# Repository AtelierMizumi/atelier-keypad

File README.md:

# Atelier6K

A 6-key mechanical keypad with 3 extra buttons, designed for osu! and usable as
a small macropad. ATmega32U4, USB-C, hot-swap sockets, per-key and underglow
RGB, QMK firmware with VIA.

**[Live demo](https://blog.minhthuan.dev/atelier-keypad/)**: switch between
rev 0, rev 1 and the planned rev 2, rotate each board in 3D, pull the case
apart, and try rapid trigger in the browser.

| Revision | State | Read |
|---|---|---|
| Rev 0 (2022, ATmega32U4) | Original files, unchanged | [Looking back at rev 0](docs/rev0-review.md), [defect review](docs/design-review.md) |
| Rev 1 (2026, RP2040) | Order files ready (ERC 0, DRC 0); not built | [How it is made](docs/rev1-board.md), [honest grade](docs/rev1-assessment.md) |
| Rev 2.0 (Hall effect, 8 kHz) | Order files, firmware and CI ready (ERC 0, DRC 0); not built; branch `plan/hall-effect` | [How to order](https://github.com/AtelierMizumi/atelier-keypad/blob/plan/hall-effect/docs/build/ordering.md), [the board](https://github.com/AtelierMizumi/atelier-keypad/blob/plan/hall-effect/docs/rev2-board.md), [bring-up](https://github.com/AtelierMizumi/atelier-keypad/blob/plan/hall-effect/docs/rev2-bringup.md) |

> [!WARNING]
> **Rev 0 is an unverified prototype.** It was designed in 2022 as a first PCB
> and has no recorded bring-up. A [design review](docs/design-review.md) found
> issues that should be fixed before anyone orders it, including a missing
> fuse and an LED chain the firmware cannot drive. Treat the files as a
> reference, not as a board ready to manufacture.

## Features

- 6 Cherry MX switches on Kailh hot-swap sockets, plus 3 tactile buttons, in a
  3 × 3 diode matrix
- Per-key reverse-mount RGB (6 LEDs) and underglow (4 LEDs)
- ATmega32U4 with a 16 MHz crystal, USB-C with ESD protection
- QMK firmware with VIA, 1000 Hz polling and runtime-adjustable debounce (rev 1 firmware)
- Stacked laser-cut acrylic case, 14 mm tall, generated from the PCB file
- 2-layer PCB, about 81 × 74 mm, hand-solderable parts (0805, SOD-123, TQFP-44)

## Renders

| Top | Bottom |
|-----|--------|
|  |  |

Schematic: [SVG](docs/images/schematic.svg)

### Case

Four laser-cut acrylic layers that follow the PCB outline and clamp the board
between them with four M3 screws. The cut files are generated from the KiCad
board, so cut-outs and screw holes always match the PCB.

| Layer | Acrylic | Job |
|-------|---------|-----|
| Switch plate | 3 mm clear | Locates the switches; top face 5.0 mm above the PCB |
| Top frame | 2 mm clear | Spacer that sets the switch height |
| Bottom frame | 5 mm frosted | Clears the sockets and spreads the underglow |
| Base | 3 mm clear | Captive M3 nuts, reset hole |

DXF files are in [`case/dxf/`](case/dxf). Materials, cutting notes and
assembly steps are in the [case design notes](docs/case.md). The case has not
been cut or test-fitted yet.

## Rev 1 (designed, not built)

`hardware/rev1/` holds the next revision: an RP2040-Zero module, 9 direct
pins, one chain of 10 SK6812MINI-E LEDs, a polyfuse and a level shifter, on
the same outline and screw holes. The schematic, board and routing are
generated from `hardware/rev1/circuit.py` by `scripts/rev1.sh` and pass
KiCad's ERC and DRC. It has not been fabricated; see
[docs/rev1-board.md](docs/rev1-board.md) for the open points before ordering.

## Repository layout

| Path | Contents |
|------|----------|
| `hardware/atelier6k/` | Rev 0 KiCad 6 project (schematic and PCB), unchanged since 2022 |
| `hardware/libs/` | Footprint and symbol libraries (git submodules) and local footprints |
| `hardware/gerbers/rev0/` | Gerbers and drill files exported in 2022 |
| `hardware/bom.csv` | Bill of materials generated from the schematic |
| `firmware/atelier6k/` | Rev 1 QMK keyboard (RP2040), runtime debounce and its tests |
| `firmware/via/` | VIA v3 definition with the debounce menu |
| `firmware/build/` | Built firmware (`atelier6k_default.uf2`) |
| `firmware/legacy-2022/` | Rev 0 firmware and its 2022 build |
| `case/` | Case generator (`generate.py`), its tests, DXF cut files; 2022 drawings in `legacy/` |
| `docs/` | Design review, case notes, ERC/DRC reports, schematic, images |
| `site/` | The demo page published to GitHub Pages |
| `scripts/` | `export.sh` regenerates all derived files; `check-assets.sh` checks image links |

Clone with submodules:

```sh
git clone --recurse-submodules https://github.com/AtelierMizumi/atelier-keypad.git
```

The original KiCad 6 files are kept under the tag `rev0-kicad6`.

## Regenerating renders and reports

`scripts/export.sh` runs `kicad-cli` (KiCad 10 or newer) from your system, or
from the official KiCad Docker image when KiCad is not installed:

```sh
./scripts/export.sh          # renders, GLB, schematic SVG, BOM, ERC/DRC, case DXF
./scripts/check-assets.sh    # fails if any image reference leaves the repo
```

## Firmware

`firmware/atelier6k/` is the rev 1 firmware for current QMK (0.34.8): RP2040,
nine direct-pin keys, one chain of ten RGB LEDs, VIA.

- **1000 Hz** USB polling.
- **Debounce adjustable at runtime**, 0–25 ms, from a slider in VIA. A press
  is reported on the scan that first sees it; the debounce time only delays
  the release. The setting is stored on the keypad.
- **Three mode layers**, osu! standard, taiko and mania, switched with a side
  button and shown by the underglow colour. Every key is remappable in VIA.
- Brightness capped at 120 of 255 to stay inside the USB current budget.

It has been compiled and its debounce logic is unit-tested, but it has **not
run on hardware**: rev 1 of the board does not exist yet. The pin assignment
in `keyboard.json` matches the routed rev 1 PCB, and a test in
`hardware/rev1/tests/` fails if the two ever disagree.

```sh
./scripts/firmware.sh        # unit tests, lint, build firmware/build/atelier6k_default.uf2
```

The script needs Docker and a QMK checkout; see the comment at its top.
To use the VIA menu, load `firmware/via/atelier6k.json` in VIA's Design tab.

The 2022 firmware for the rev 0 ATmega32U4 board is kept in
`firmware/legacy-2022/`; it does not build on current QMK.

## License

- Hardware (`hardware/`, `case/`): [CERN-OHL-P v2](LICENSES/CERN-OHL-P-2.0.txt)
- Firmware (`firmware/`): [GPL-2.0-or-later](LICENSES/GPL-2.0-or-later.txt), as required by QMK
- Third-party libraries under `hardware/libs/` keep their own licenses

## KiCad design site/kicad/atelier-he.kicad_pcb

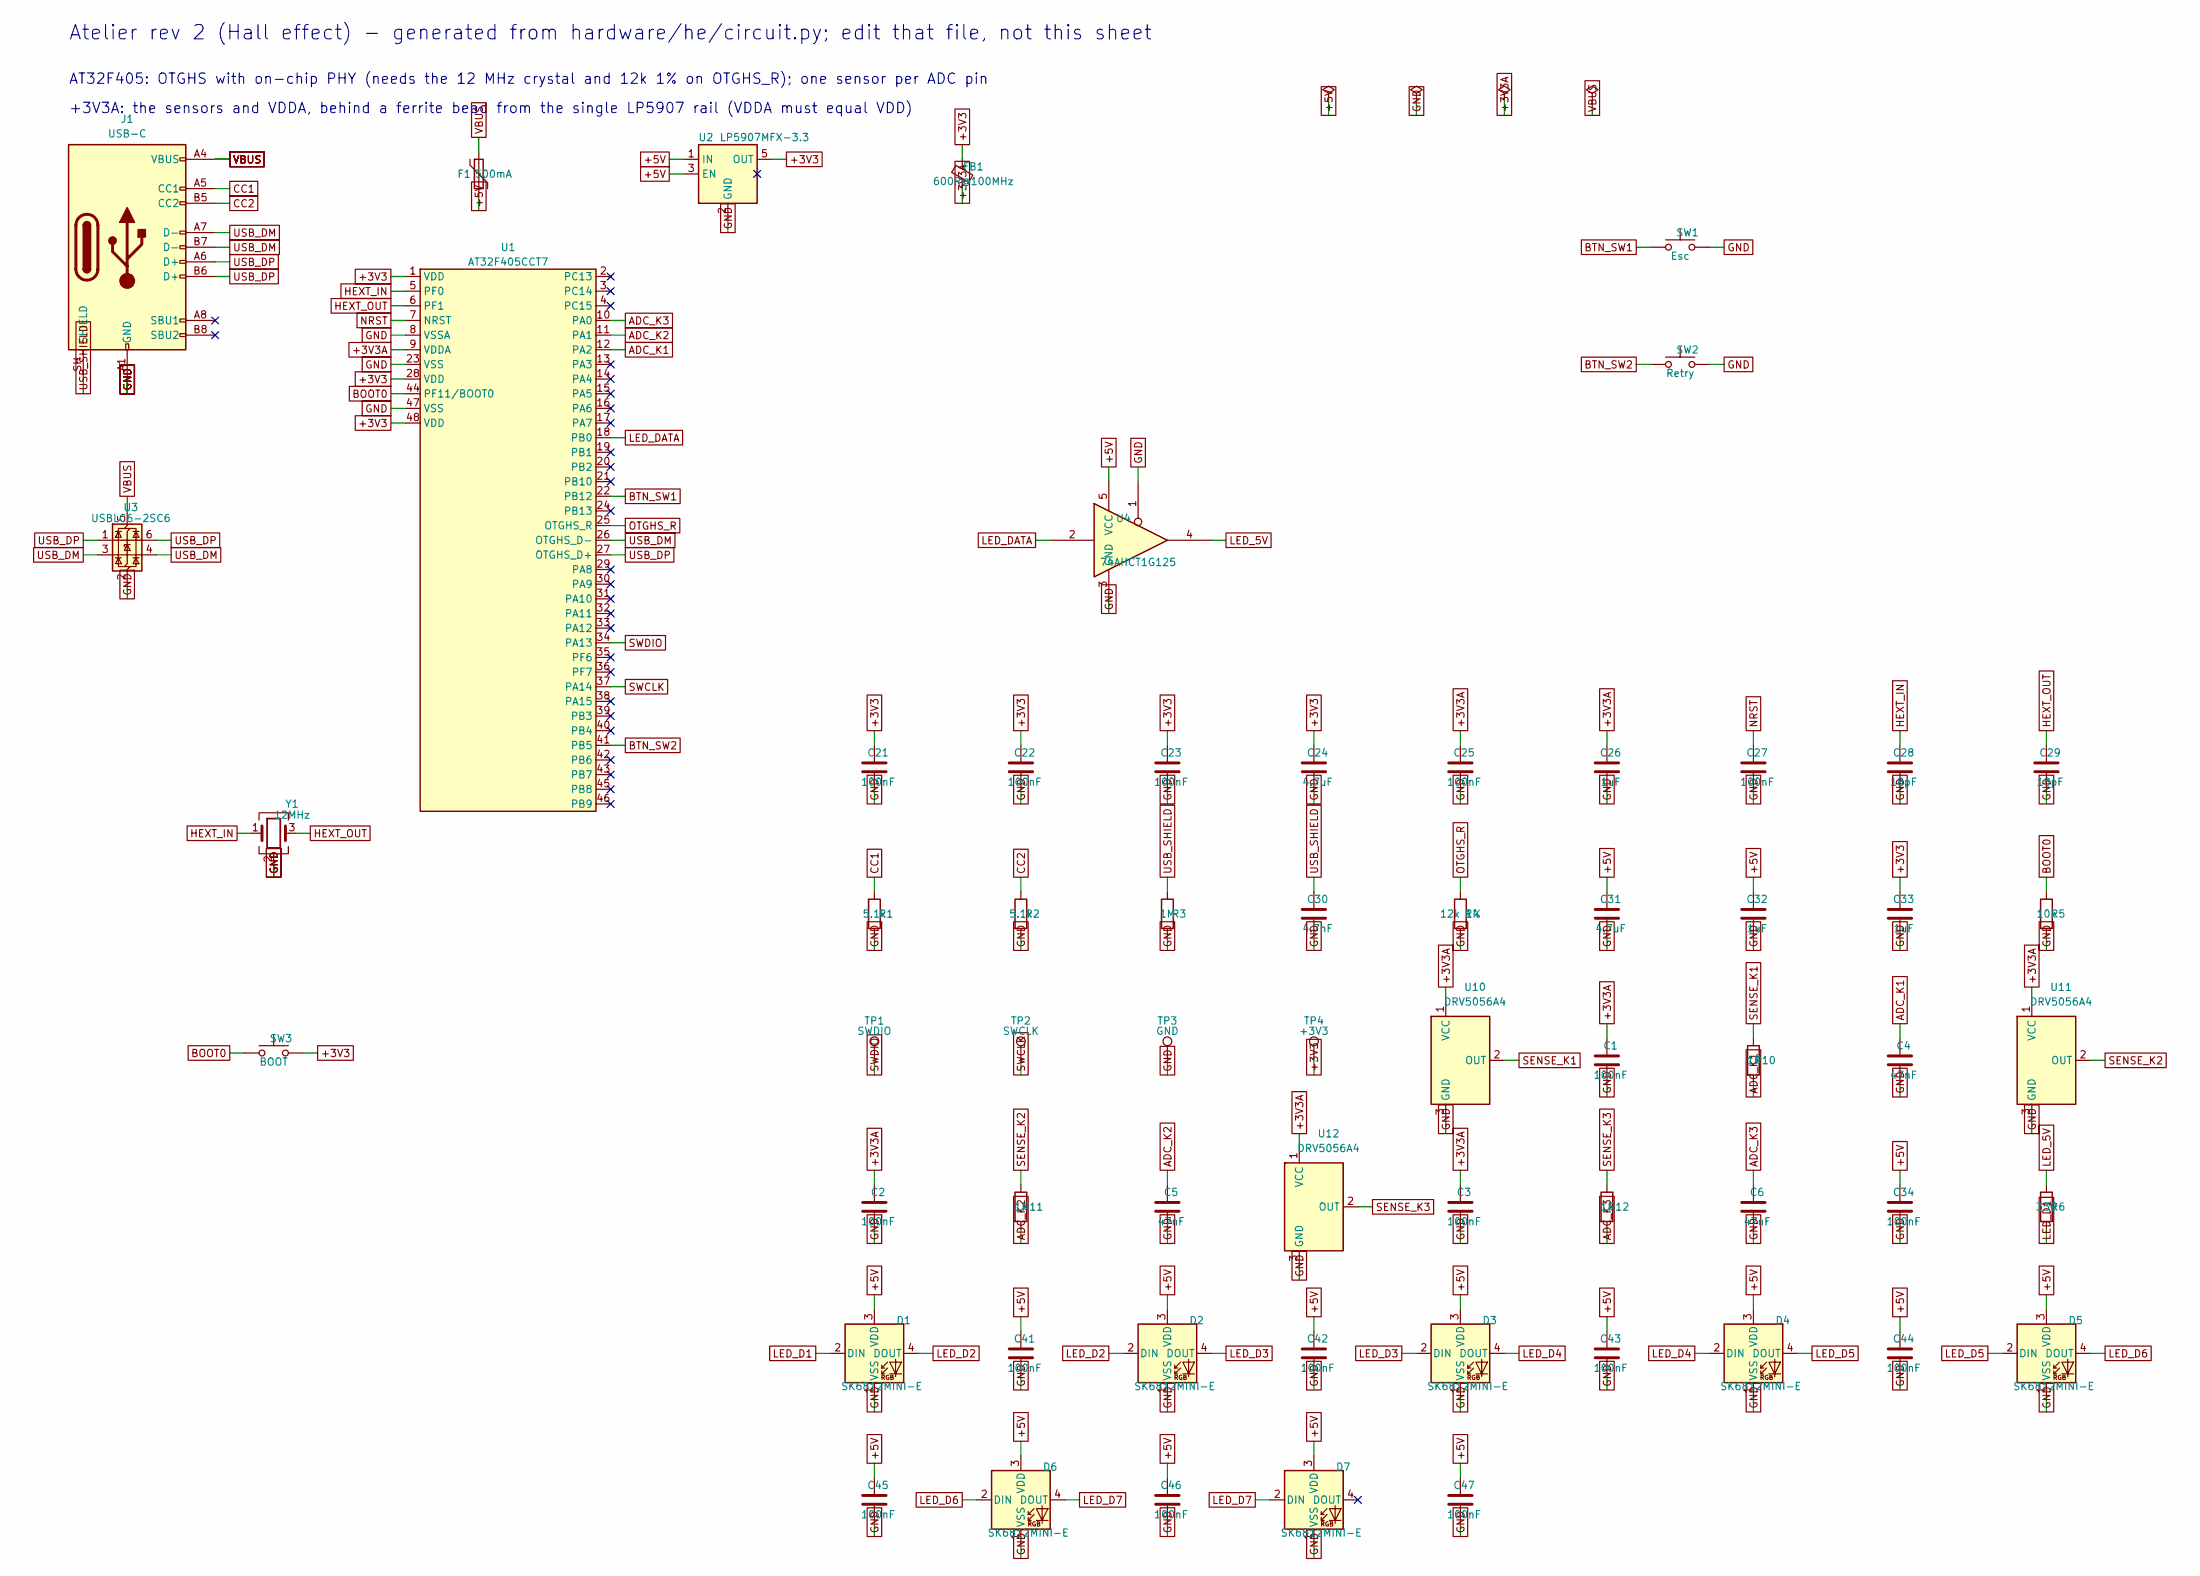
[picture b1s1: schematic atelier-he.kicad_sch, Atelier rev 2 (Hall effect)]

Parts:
C1, C2, C3, C21, C22, C23, C25, C27, C34, C41, C42, C43, C44, C45, C46, C47: 100nF; C_0603_1608Metric_Pad1.08x0.95mm_HandSolder
C4, C5, C6: 47nF; C_0603_1608Metric_Pad1.08x0.95mm_HandSolder
C24, C31: 4.7uF; C_0805_2012Metric_Pad1.18x1.45mm_HandSolder
C26, C32, C33: 1uF; C_0603_1608Metric_Pad1.08x0.95mm_HandSolder
C28, C29: 18pF; C_0603_1608Metric_Pad1.08x0.95mm_HandSolder
C30: 4.7nF; C_0603_1608Metric_Pad1.08x0.95mm_HandSolder
D1, D2, D3, D4, D5, D6, D7: SK6812MINI-E; LED_SK6812MINI-E_3.2x2.8mm_P1.5mm_ReverseMount
F1: 500mA; Fuse_1206_3216Metric_Pad1.42x1.75mm_HandSolder
FB1: 600R@100MHz; L_0603_1608Metric
J1: USB-C; USB_C_Receptacle_HRO_TYPE-C-31-M-12
R1: 5.1k; R_0402_1005Metric
R2: 5.1k; R_0603_1608Metric_Pad0.98x0.95mm_HandSolder
R3: 1M; R_0603_1608Metric_Pad0.98x0.95mm_HandSolder
R4: 12k 1%; R_0603_1608Metric_Pad0.98x0.95mm_HandSolder
R5: 10k; R_0603_1608Metric_Pad0.98x0.95mm_HandSolder
R6: 330; R_0603_1608Metric_Pad0.98x0.95mm_HandSolder
R10, R11, R12: 1k; R_0603_1608Metric_Pad0.98x0.95mm_HandSolder
SW1: Esc; SW_PUSH_6mm_H7.3mm
SW2: Retry; SW_PUSH_6mm_H7.3mm
SW3: BOOT; SW_SPST_TL3342
TP1: SWDIO; TestPoint_Pad_1.0x1.0mm
TP2: SWCLK; TestPoint_Pad_1.0x1.0mm
TP3: GND; TestPoint_Pad_1.0x1.0mm
TP4: +3V3; TestPoint_Pad_1.0x1.0mm
U1: AT32F405CCT7; LQFP-48_7x7mm_P0.5mm
U2: LP5907MFX-3.3; SOT-23-5
U3: USBLC6-2SC6; SOT-23-6
U4: 74AHCT1G125; SOT-23-5
U10, U11, U12: DRV5056A4; SOT-23
Y1: 12MHz; Crystal_SMD_3225-4Pin_3.2x2.5mm

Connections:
+3V3: C21.1, C22.1, C23.1, C24.1, C33.1, FB1.1, SW3.2, TP4.1, U1.1 (VDD), U1.28 (VDD), U1.48 (VDD), U2.5 (OUT)
+3V3A: C1.1, C2.1, C3.1, C25.1, C26.1, FB1.2, U1.9 (VDDA), U10.1 (VCC), U11.1 (VCC), U12.1 (VCC)
+5V: C31.1, C32.1, C34.1, C41.1, C42.1, C43.1, C44.1, C45.1, C46.1, C47.1, D1.3 (VDD), D2.3 (VDD), D3.3 (VDD), D4.3 (VDD), D5.3 (VDD), D6.3 (VDD), D7.3 (VDD), F1.2, U2.1 (IN), U2.3 (EN), U4.5 (VCC)
ADC_K1: C4.1, R10.2, U1.12 (PA2)
ADC_K2: C5.1, R11.2, U1.11 (PA1)
ADC_K3: C6.1, R12.2, U1.10 (PA0)
BOOT0: R5.1, SW3.1, U1.44 (PF11/BOOT0)
BTN_SW1: SW1.1, U1.22 (PB12)
BTN_SW2: SW2.1, U1.41 (PB5)
CC1: J1.A5 (CC1), R1.1
CC2: J1.B5 (CC2), R2.1
GND: C1.2, C2.2, C3.2, C4.2, C5.2, C6.2, C21.2, C22.2, C23.2, C24.2, C25.2, C26.2, C27.2, C28.2, C29.2, C30.2, C31.2, C32.2, C33.2, C34.2, C41.2, C42.2, C43.2, C44.2, C45.2, C46.2, C47.2, D1.1 (VSS), D2.1 (VSS), D3.1 (VSS), D4.1 (VSS), D5.1 (VSS), D6.1 (VSS), D7.1 (VSS), J1.A1 (GND), J1.A12 (GND), J1.B1 (GND), J1.B12 (GND), R1.2, R2.2, R3.2, R4.2, R5.2, SW1.2, SW2.2, TP3.1, U1.8 (VSSA), U1.23 (VSS), U1.47 (VSS), U2.2 (GND), U3.2 (GND), U4.1, U4.3 (GND), U10.3 (GND), U11.3 (GND), U12.3 (GND), Y1.2 (G), Y1.4 (G)
HEXT_IN: C28.1, U1.5 (PF0), Y1.1
HEXT_OUT: C29.1, U1.6 (PF1), Y1.3
LED_5V: R6.1, U4.4
LED_D1: D1.2 (DIN), R6.2
LED_D2: D1.4 (DOUT), D2.2 (DIN)
LED_D3: D2.4 (DOUT), D3.2 (DIN)
LED_D4: D3.4 (DOUT), D4.2 (DIN)
LED_D5: D4.4 (DOUT), D5.2 (DIN)
LED_D6: D5.4 (DOUT), D6.2 (DIN)
LED_D7: D6.4 (DOUT), D7.2 (DIN)
LED_DATA: U1.18 (PB0), U4.2
NRST: C27.1, U1.7 (NRST)
OTGHS_R: R4.1, U1.25 (OTGHS_R)
SENSE_K1: R10.1, U10.2 (OUT)
SENSE_K2: R11.1, U11.2 (OUT)
SENSE_K3: R12.1, U12.2 (OUT)
SWCLK: TP2.1, U1.37 (PA14)
SWDIO: TP1.1, U1.34 (PA13)
USB_DM: J1.A7 (D-), J1.B7 (D-), U1.26 (OTGHS_D-), U3.3 (I/O2), U3.4 (I/O2)
USB_DP: J1.A6 (D+), J1.B6 (D+), U1.27 (OTGHS_D+), U3.1 (I/O1), U3.6 (I/O1)
USB_SHIELD: C30.1, J1.SH (SHIELD), R3.1
VBUS: F1.1, J1.A4 (VBUS), J1.A9 (VBUS), J1.B4 (VBUS), J1.B9 (VBUS), U3.5 (VBUS)

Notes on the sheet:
Atelier rev 2 (Hall effect) - generated from hardware/he/circuit.py; edit that file, not this sheet
AT32F405: OTGHS with on-chip PHY (needs the 12 MHz crystal and 12k 1% on OTGHS_R); one sensor per ADC pin
+3V3A: the sensors and VDDA, behind a ferrite bead from the single LP5907 rail (VDDA must equal VDD)

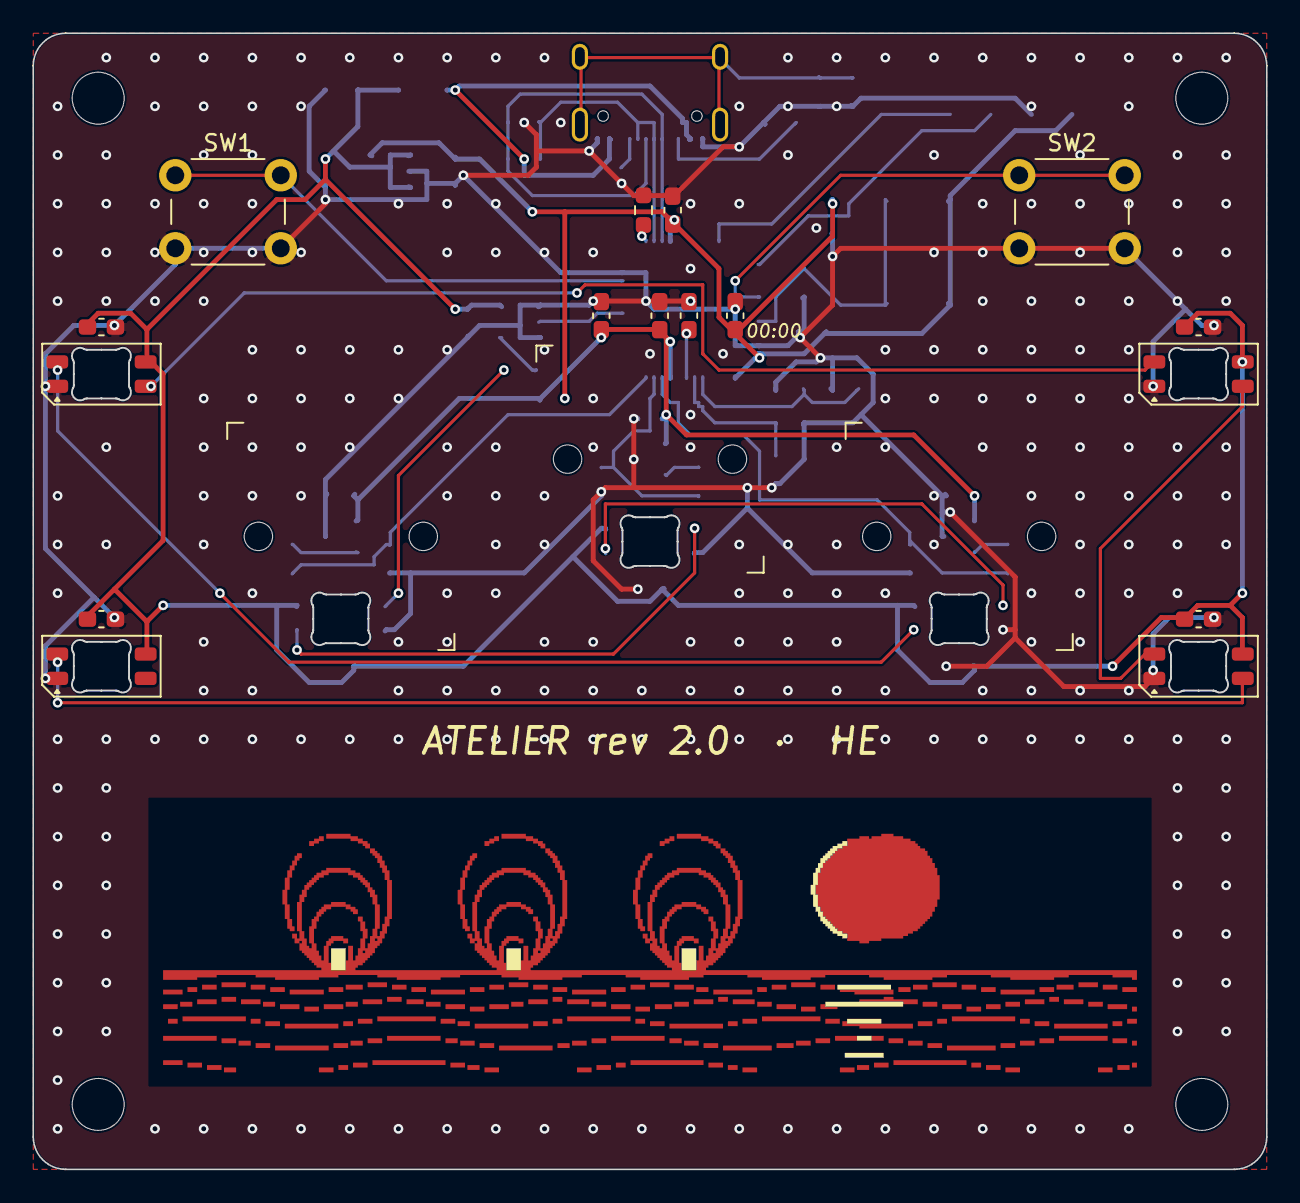
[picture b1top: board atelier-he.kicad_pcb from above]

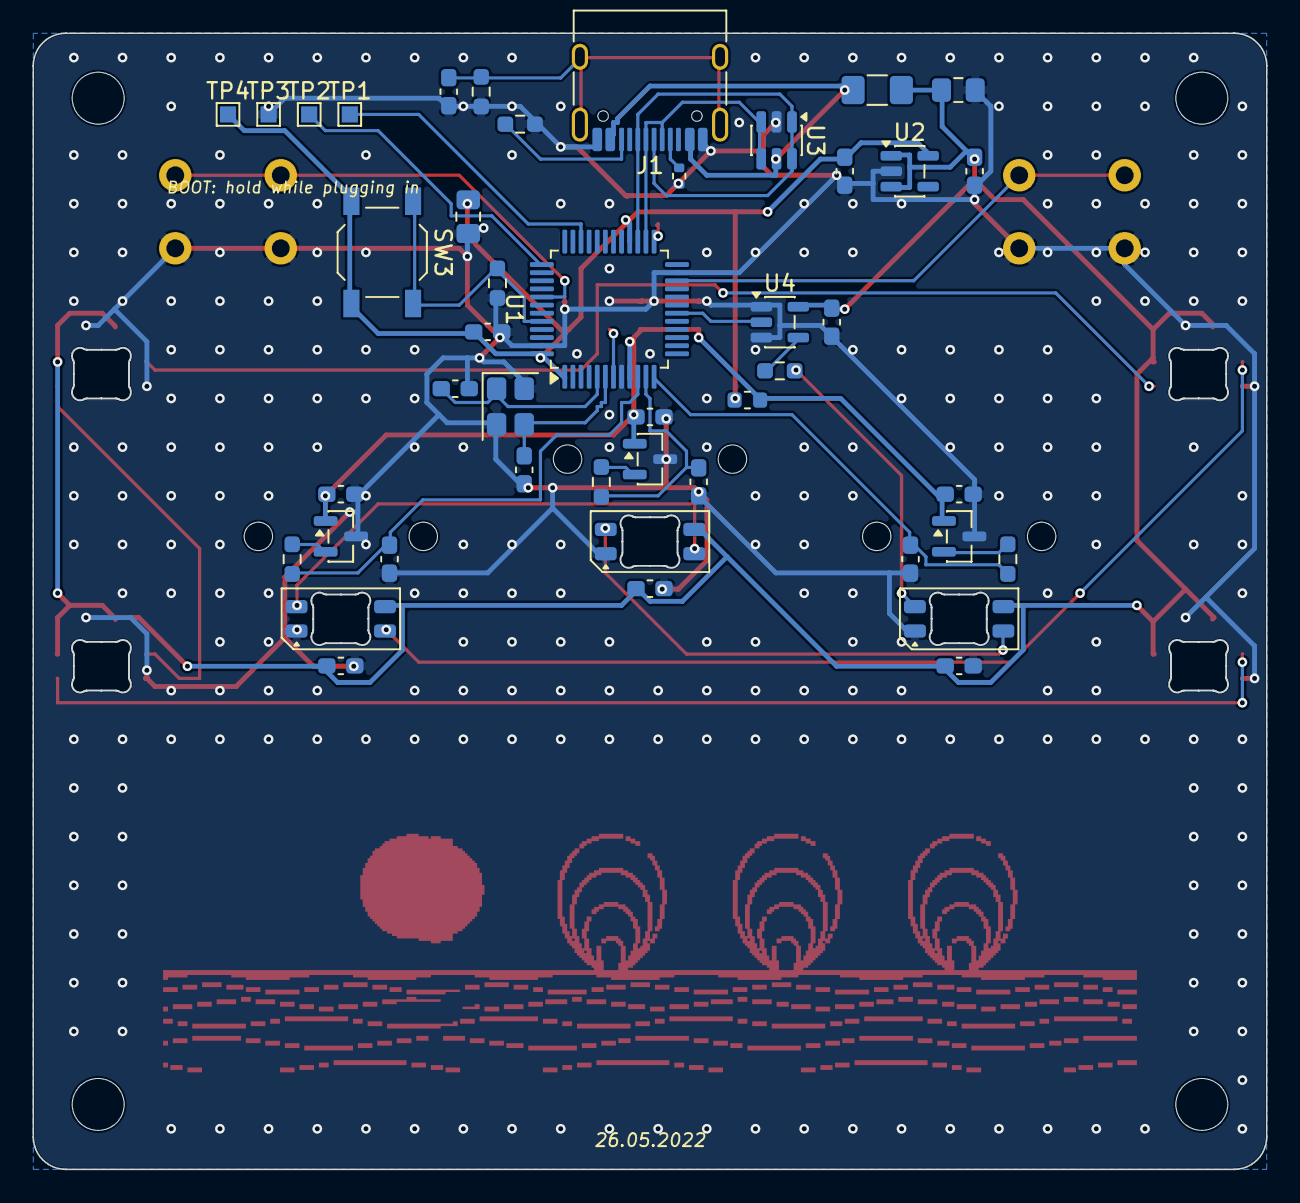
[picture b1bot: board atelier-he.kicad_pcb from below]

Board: 2 copper layers, 76.0 x 70.0 mm, 69 parts (45 on the bottom side), 34 nets.

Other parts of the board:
ART1: moon over the sea; ART_moon_sea_F
H1, H2, H3, H4: M3 nylon; MountingHole_3.2mm_M3
SW_K1, SW_K2, SW_K3: Gateron Magnetic Jade; HE_Switch_PCBMount

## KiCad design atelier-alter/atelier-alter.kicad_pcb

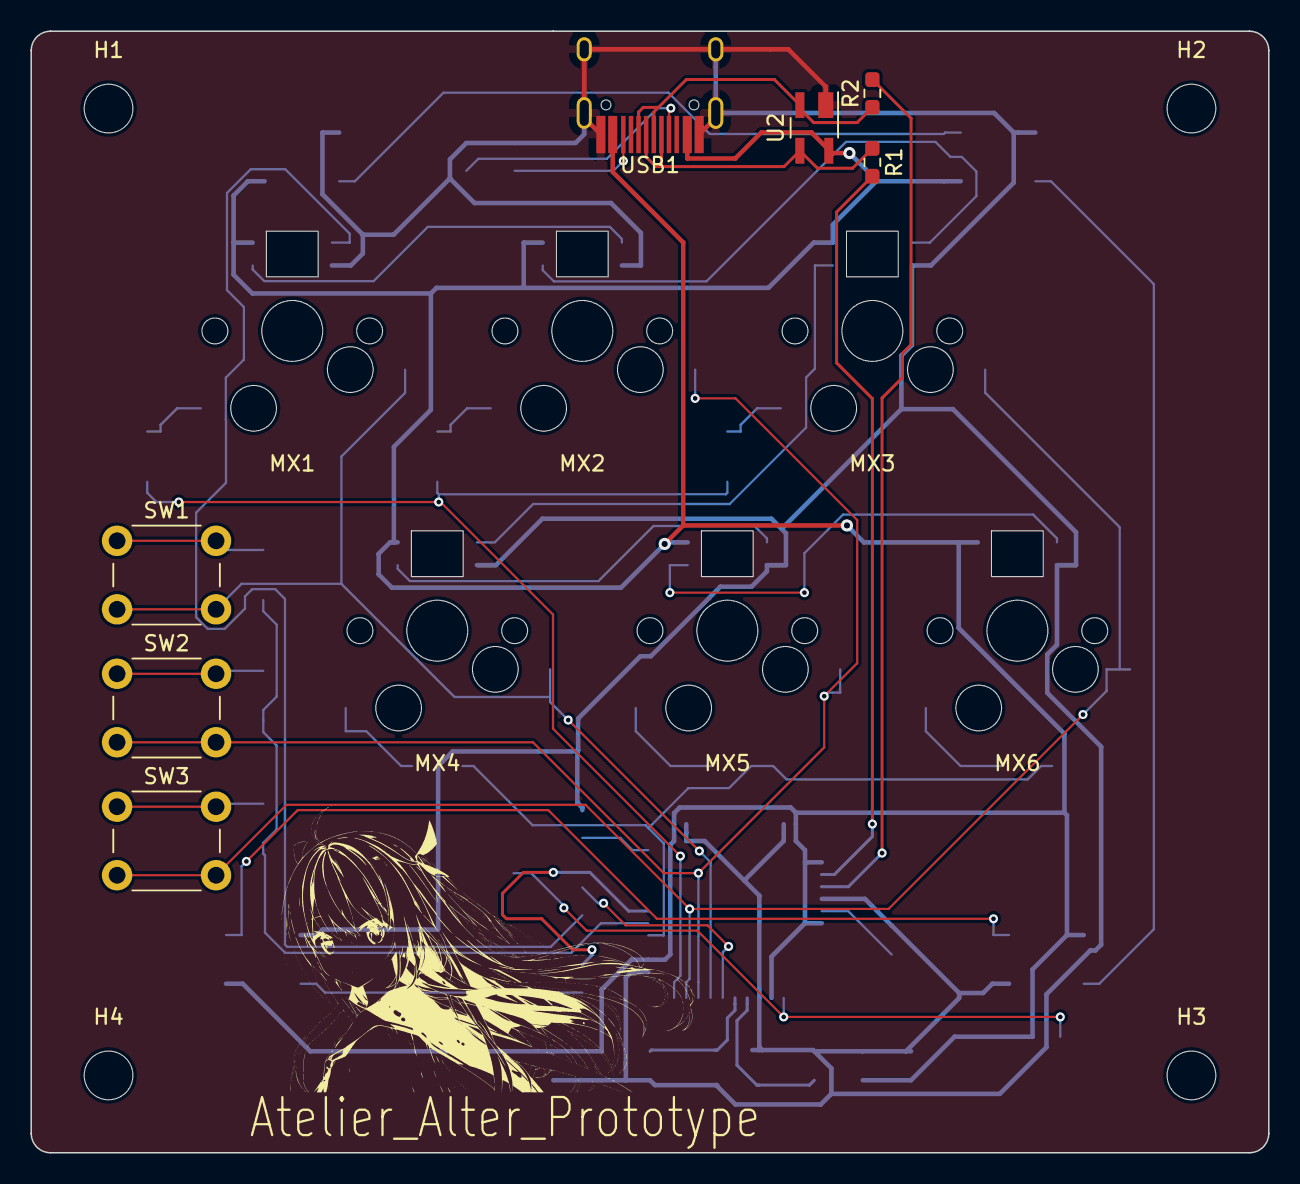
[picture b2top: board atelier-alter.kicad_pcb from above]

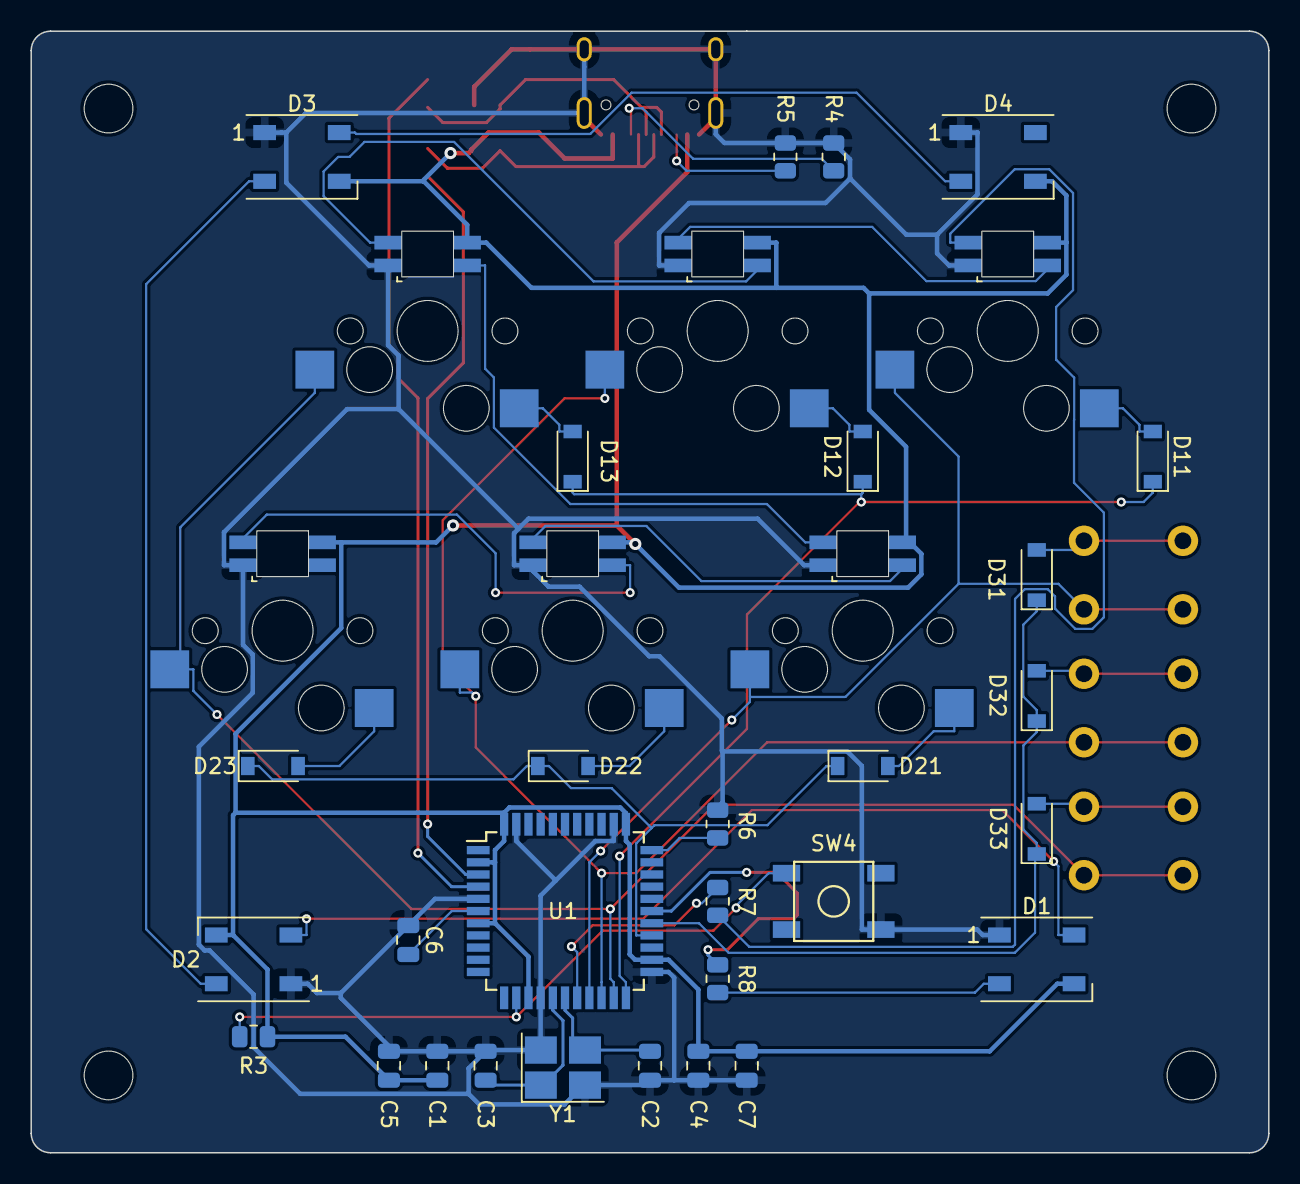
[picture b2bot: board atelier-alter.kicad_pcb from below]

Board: 2 copper layers, 81.3 x 73.7 mm, 47 parts (29 on the bottom side), 40 nets.

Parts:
Atorie': LOGO; Alter_Drawing
C1, C4, C5: 0.1uF; C_0805_2012Metric
C2, C3: 22pF; C_0805_2012Metric
C6: 1uF; C_0805_2012Metric
C7: 10uF; C_0805_2012Metric
D1, D2, D3, D4: SK6812 / WS2812B; LED_WS2812B_PLCC4_5.0x5.0mm_P3.2mm
D11, D12, D13, D21, D22, D23, D31, D32, D33: SOD-123; D_SOD-123
H1, H2, H3, H4: MountingHole; MountingHole_3.2mm_M3_ISO7380
MX1, MX2, MX3, MX4, MX5, MX6: Cherry_MX_Cherry_MX_RGB; Cherry-MX_PCB-Mounted_LTST-A683CEGBW_Kailh_Socket
R1, R2: 22; R_0603_1608Metric_Pad0.98x0.95mm_HandSolder
R3, R6: 10k; R_0805_2012Metric
R4, R5: 5.1k; R_0805_2012Metric
R7, R8: 300; R_0805_2012Metric
SW1, SW2, SW3: SW_DPST; SW_PUSH_6mm_H13mm
SW4: RESET; SKQG-1155865
U1: ATmega32U4-A; TQFP-44_10x10mm_P0.8mm
U2: PRTR5V0U2X; SOT-143_Handsoldering
USB1: HRO-TYPE-C-31-M-12; HRO-TYPE-C-31-M-12-HandSoldering
Y1: 16Mhz; Crystal_SMD_3225-4Pin_3.2x2.5mm_HandSoldering

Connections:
+5V: C1.1, C4.1, C5.1, C7.1, D1.3 (VDD), D2.3 (VDD), D3.3 (VDD), D4.3 (VDD), MX1.4 (VCC), MX2.4 (VCC), MX3.4 (VCC), MX4.4 (VCC), MX5.4 (VCC), MX6.4 (VCC), R3.2, U1.2 (UVCC), U1.7 (VBUS), U1.14 (VCC), U1.24 (AVCC), U1.34 (VCC), U1.44 (AVCC), U2.4 (VCC), USB1.2 (VBUS), USB1.11 (VBUS)
BackRGB: D1.2 (DIN), R8.2
COL1: MX1.5 (SW1), MX4.5 (SW1), SW1.2, U1.19 (PD1)
COL2: MX2.5 (SW1), MX5.5 (SW1), SW2.2, U1.20 (PD2)
COL3: MX3.5 (SW1), MX6.5 (SW1), SW3.2, U1.21 (PD3)
D12: MX3.3 (DOUT), MX4.2 (DIN)
D+: R2.1, U2.2 (IO1), USB1.6 (DP1), USB1.8 (DP2)
D-: R1.1, U2.3 (IO2), USB1.5 (DN2), USB1.7 (DN1)
GND: C1.2, C2.1, C3.1, C4.2, C5.2, C6.1, C7.2, D1.1 (VSS), D2.1 (VSS), D3.1 (VSS), D4.1 (VSS), MX1.1 (GND), MX2.1 (GND), MX3.1 (GND), MX4.1 (GND), MX5.1 (GND), MX6.1 (GND), R4.1, R5.1, R6.2, SW4.1, U1.5 (UGND), U1.15 (GND), U1.23 (GND), U1.35 (GND), U1.43 (GND), U2.1 (GND), USB1.1 (GND), USB1.12 (GND), USB1.13 (SHIELD), Y1.2, Y1.4
InKeyRGB: MX1.2 (DIN), R7.2
unnamed: C2.2, U1.17 (XTAL1), Y1.3
unnamed: C3.2, U1.16 (XTAL2), Y1.1
unnamed: C6.2, U1.6 (UCAP)
unnamed: D1.4 (DOUT), D2.2 (DIN)
unnamed: D2.4 (DOUT), D3.2 (DIN)
unnamed: D3.4 (DOUT), D4.2 (DIN)
unnamed: D11.2 (A), MX1.6 (SW2)
unnamed: D12.2 (A), MX2.6 (SW2)
unnamed: D13.2 (A), MX3.6 (SW2)
unnamed: D21.2 (A), MX4.6 (SW2)
unnamed: D22.2 (A), MX5.6 (SW2)
unnamed: D23.2 (A), MX6.6 (SW2)
unnamed: D31.2 (A), SW1.1
unnamed: D32.2 (A), SW2.1
unnamed: D33.2 (A), SW3.1
unnamed: MX1.3 (DOUT), MX2.2 (DIN)
unnamed: MX2.3 (DOUT), MX3.2 (DIN)
unnamed: MX4.3 (DOUT), MX5.2 (DIN)
unnamed: MX5.3 (DOUT), MX6.2 (DIN)
unnamed: R1.2, U1.3 (D-)
unnamed: R2.2, U1.4 (D+)
unnamed: R3.1, SW4.2, U1.13 (~RESET)
unnamed: R4.2, USB1.4 (CC1)
unnamed: R5.2, USB1.10 (CC2)
unnamed: R6.1, U1.33 (~HWB/PE2)
unnamed: R7.1, U1.18 (PD0)
unnamed: R8.1, U1.28 (PB4)
ROW1: D11.1 (K), D12.1 (K), D13.1 (K), U1.22 (PD5)
ROW2: D21.1 (K), D22.1 (K), D23.1 (K), U1.26 (PD6)
ROW3: D31.1 (K), D32.1 (K), D33.1 (K), U1.27 (PD7)

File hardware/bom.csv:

"Refs","Value","Footprint","Qty"
"C1,C4,C5","0.1uF","Capacitor_SMD:C_0805_2012Metric","3"
"C2,C3","22pF","Capacitor_SMD:C_0805_2012Metric","2"
"C6","1uF","Capacitor_SMD:C_0805_2012Metric","1"
"C7","10uF","Capacitor_SMD:C_0805_2012Metric","1"
"D1,D2,D3,D4","SK6812 {slash} WS2812B","LED_SMD:LED_WS2812B_PLCC4_5.0x5.0mm_P3.2mm","4"
"D11,D12,D13,D21,D22,D23,D31,D32,D33","SOD-123","Diode_SMD:D_SOD-123","9"
"H1,H2,H3,H4","MountingHole","MountingHole:MountingHole_3.2mm_M3_ISO7380","4"
"MX1,MX2,MX3,MX4,MX5,MX6","Cherry_MX_Cherry_MX_RGB","Cherry MX:Cherry-MX_PCB-Mounted_LTST-A683CEGBW_Kailh_Socket","6"
"R1,R2","22","Resistor_SMD:R_0603_1608Metric_Pad0.98x0.95mm_HandSolder","2"
"R3,R6","10k","Resistor_SMD:R_0805_2012Metric","2"
"R4,R5","5.1k","Resistor_SMD:R_0805_2012Metric","2"
"R7,R8","300","Resistor_SMD:R_0805_2012Metric","2"
"SW1,SW2,SW3","SW_DPST","Button_Switch_THT:SW_PUSH_6mm_H13mm","3"
"SW4","RESET","random-keyboard-parts:SKQG-1155865","1"
"U1","ATmega32U4-A","Package_QFP:TQFP-44_10x10mm_P0.8mm","1"
"U2","PRTR5V0U2X","Package_TO_SOT_SMD:SOT-143_Handsoldering","1"
"USB1","HRO-TYPE-C-31-M-12","Type-C:HRO-TYPE-C-31-M-12-HandSoldering","1"
"Y1","16Mhz","Crystal:Crystal_SMD_3225-4Pin_3.2x2.5mm_HandSoldering","1"

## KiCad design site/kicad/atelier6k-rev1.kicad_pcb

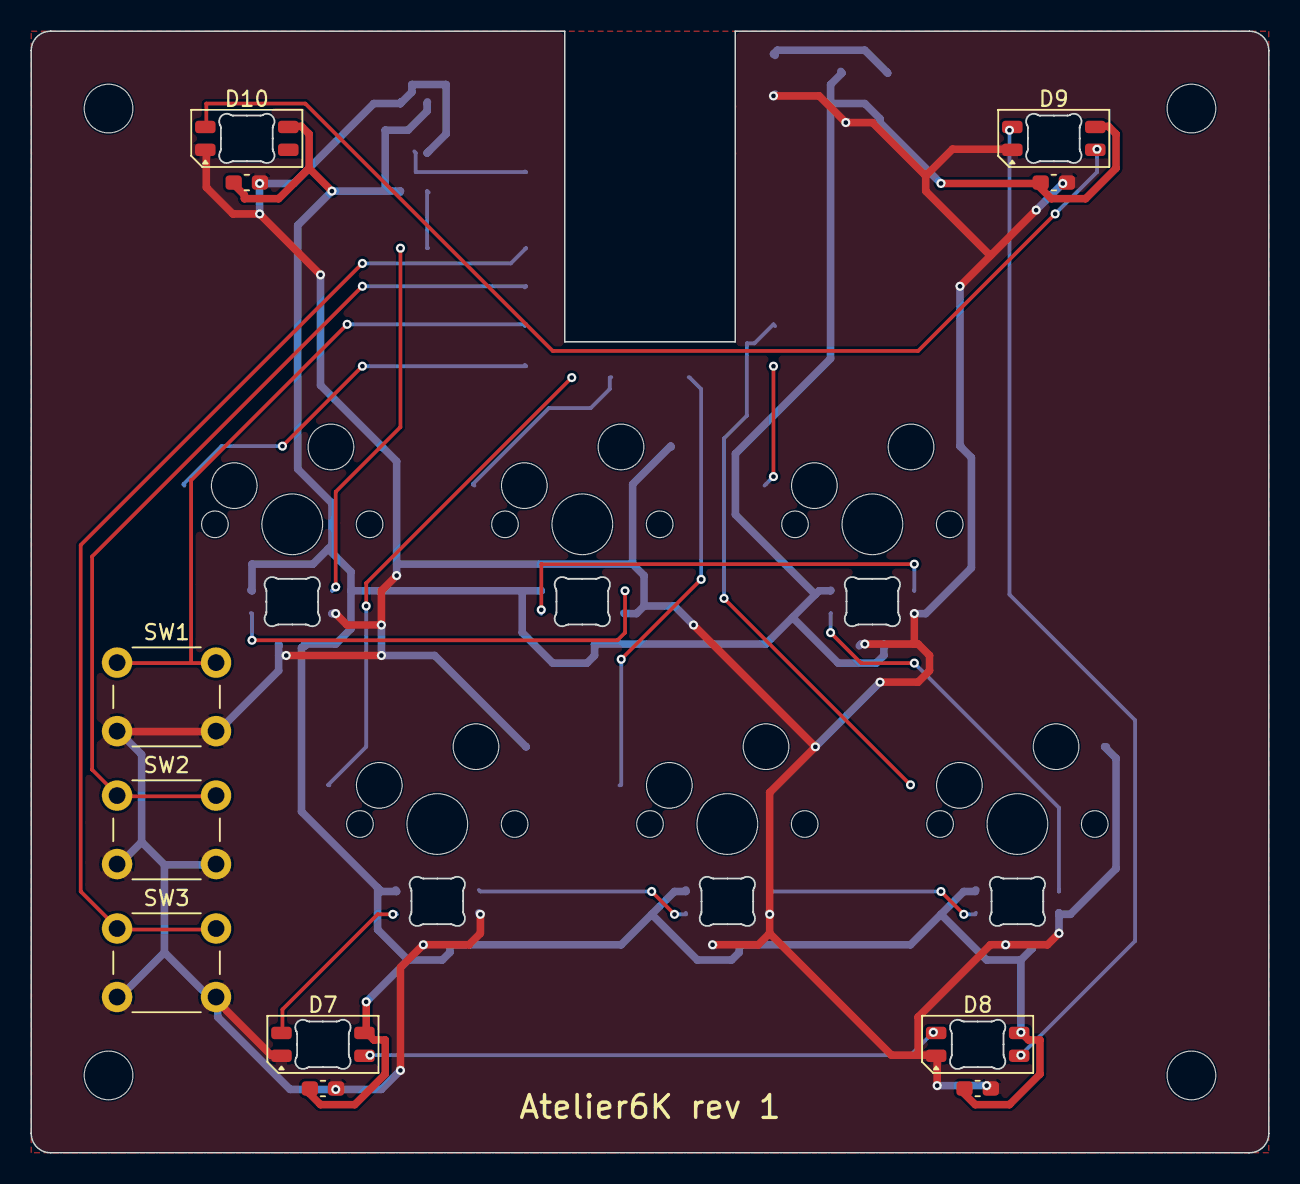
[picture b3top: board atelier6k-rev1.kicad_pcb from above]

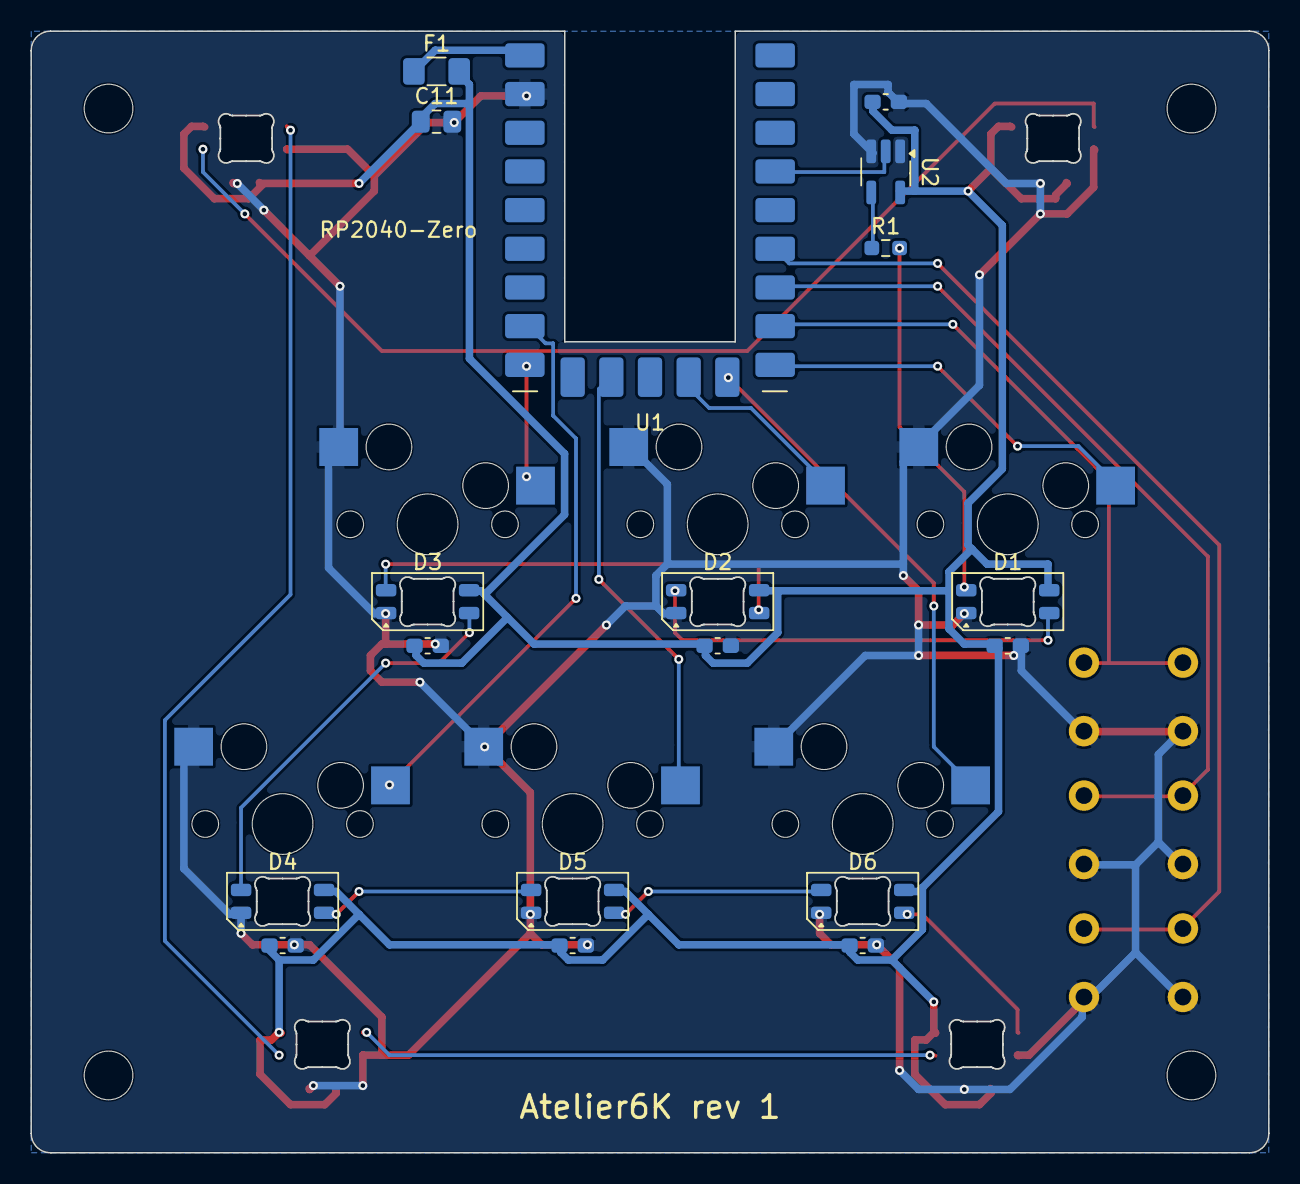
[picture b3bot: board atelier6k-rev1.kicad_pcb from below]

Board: 2 copper layers, 81.3 x 73.7 mm, 39 parts (18 on the bottom side), 24 nets.

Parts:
C1, C2, C3, C4, C5, C6, C7, C8, C9, C10, C12: 100nF; C_0603_1608Metric_Pad1.08x0.95mm_HandSolder
C11: 4.7uF; C_0805_2012Metric_Pad1.18x1.45mm_HandSolder
D1, D2, D3, D4, D5, D6, D7, D8, D9, D10: SK6812MINI-E; LED_SK6812MINI-E_3.2x2.8mm_P1.5mm_ReverseMount
F1: 500mA; Fuse_1206_3216Metric_Pad1.42x1.75mm_HandSolder
H1, H2, H3, H4: M3; MountingHole_3.2mm_M3
MX1, MX2, MX3, MX4, MX5, MX6: MX hot-swap; MXOnly-1U-Hotswap
R1: 330; R_0603_1608Metric_Pad0.98x0.95mm_HandSolder
SW1, SW2, SW3: 6x6 tact; SW_PUSH_6mm_H13mm
U1: RP2040-Zero; RP2040-Zero_Flush
U2: 74AHCT1G125; SOT-23-5_HandSoldering

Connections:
+5V: C1.1, C2.1, C3.1, C4.1, C5.1, C6.1, C7.1, C8.1, C9.1, C10.1, C11.1, C12.1, D1.3, D2.3, D3.3, D4.3, D5.3, D6.3, D7.3, D8.3, D9.3, D10.3, F1.2, U2.5
B1: SW1.1, U1.GP7
B2: SW2.1, U1.GP6
B3: SW3.1, U1.GP5
GND: C1.2, C2.2, C3.2, C4.2, C5.2, C6.2, C7.2, C8.2, C9.2, C10.2, C11.2, C12.2, D1.1, D2.1, D3.1, D4.1, D5.1, D6.1, D7.1, D8.1, D9.1, D10.1, MX1.2, MX2.2, MX3.2, MX4.2, MX5.2, MX6.2, SW1.2, SW2.2, SW3.2, U1.GND, U2.1, U2.3
K1: MX1.1, U1.GP8
K2: MX2.1, U1.GP10
K3: MX3.1, U1.GP14
K4: MX4.1, U1.GP9
K5: MX5.1, U1.GP12
K6: MX6.1, U1.GP15
LED_5V: R1.1, U2.4
LED_D1: D1.2, R1.2
LED_D2: D1.4, D2.2
LED_D3: D2.4, D3.2
LED_D4: D3.4, D4.2
LED_D5: D4.4, D5.2
LED_D6: D5.4, D6.2
LED_D7: D6.4, D7.2
LED_D8: D7.4, D8.2
LED_D9: D8.4, D9.2
LED_D10: D9.4, D10.2
LED_DATA: U1.GP3, U2.2
VBUS: F1.1, U1.5V

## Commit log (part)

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2022-05-25 get go
2022-05-25 add files
2022-05-25 add submodules
2022-05-25 add main things
2022-05-26 redrawn
2022-05-26 da route thu nghiem xong xuoi
2022-05-27 redrawn lan 3, them vai chuc nang
2022-05-27 tham khao them tu board vcl6k
2022-05-27 kaka, rat manh
2022-05-27 add essentials
2022-05-27 phai them cai db nay moi chiu
2022-05-27 update footprint, route lai mach, giam manh so luong vias
2022-05-27 xuat file gerber de in
2022-05-27 doc tao . md
2022-05-27 get go #2
2022-05-28 add M2 mounting hole
2022-05-28 rework mot chut
2022-05-28 update doc tao di . md
2022-05-28 xuat file gerber dong bo
2022-05-29 doc tao . md and stuff
2022-05-31 small tweaks, done drawing the case
2022-06-02 minor updates here and there
2022-06-03 decided to nuke all led capacitor
2022-06-03 van la doc tao . md
2022-06-04 add qmp firmware files
2022-06-04 update pcb + qmk firmware
2022-06-18 final commit for rev 0.
2022-06-18 final
